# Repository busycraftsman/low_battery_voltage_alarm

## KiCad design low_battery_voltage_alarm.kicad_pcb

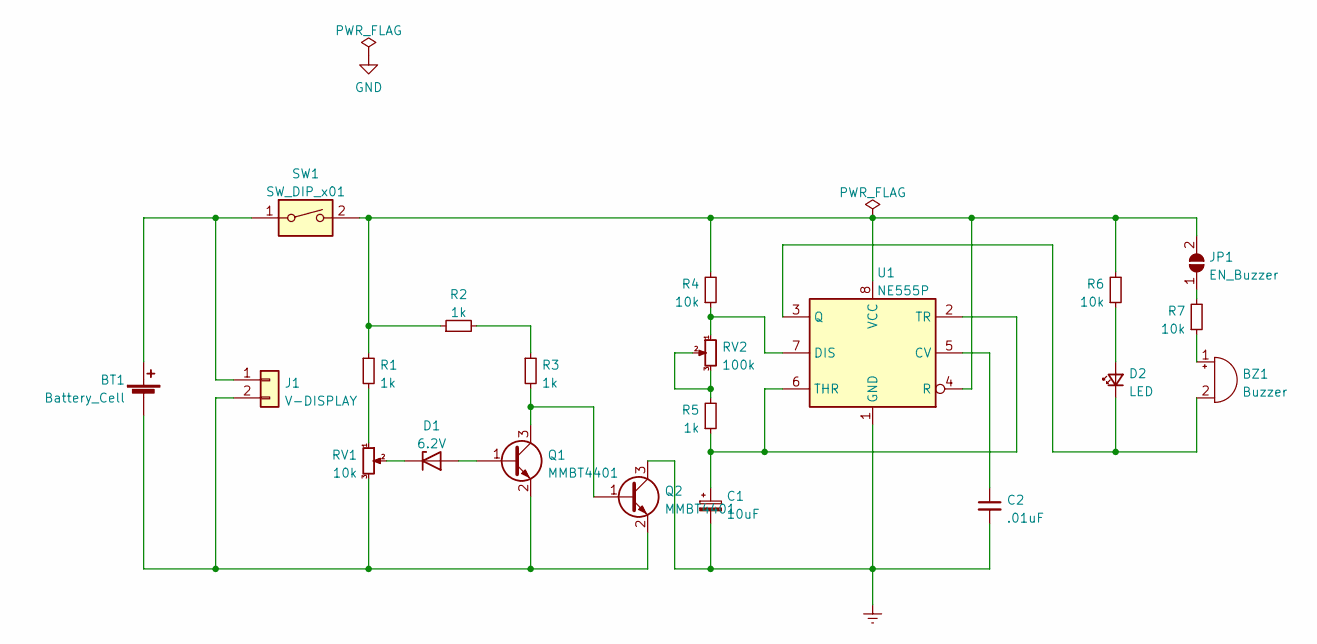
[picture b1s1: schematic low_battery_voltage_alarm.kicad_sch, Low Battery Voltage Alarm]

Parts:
BT1: Battery_Cell; JST_XH_S2B-XH-A-1_1x02_P2.50mm_Horizontal
BZ1: Buzzer; Buzzer_12x9.5RM7.6
C1: 10uF; CP_Radial_D5.0mm_P2.50mm
C2: .01uF; C_0805_2012Metric_Pad1.18x1.45mm_HandSolder
D1: 6.2V; D_DO-35_SOD27_P7.62mm_Horizontal
D2: LED; LED_D1.8mm_W3.3mm_H2.4mm
J1: V-DISPLAY; JST_XH_S2B-XH-A-1_1x02_P2.50mm_Horizontal
JP1: EN_Buzzer; SolderJumper-2_P1.3mm_Open_RoundedPad1.0x1.5mm
Q1, Q2: MMBT4401; SOT-23
R1, R2, R3, R5: 1k; R_0805_2012Metric_Pad1.20x1.40mm_HandSolder
R4, R6, R7: 10k; R_0805_2012Metric_Pad1.20x1.40mm_HandSolder
RV1: 10k; Potentiometer_Runtron_RM-065_Vertical
RV2: 100k; Potentiometer_Runtron_RM-065_Vertical
SW1: SW_DIP_x01; SolderWire-0.1sqmm_1x02_P3.6mm_D0.4mm_OD1mm
U1: NE555P; DIP-8_W7.62mm

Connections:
GNDREF: C1.2, C2.2, Q2.3 (C), U1.1 (GND)
unnamed: BT1.1 (+), J1.1, SW1.1
unnamed: BT1.2 (-), J1.2, Q1.2 (E), Q2.2 (E), RV1.3
unnamed: BZ1.1 (-), R7.1
unnamed: BZ1.2 (+), D2.1 (K), U1.3 (Q)
unnamed: C1.1, R5.1, U1.2 (TR), U1.6 (THR)
unnamed: C2.1, U1.5 (CV)
unnamed: D1.1 (K), RV1.2
unnamed: D1.2 (A), Q1.1 (B)
unnamed: D2.2 (A), R6.1
unnamed: Q1.3 (C), Q2.1 (B), R3.2
unnamed: JP1.2 (B), R1.1, R2.1, R4.2, R6.2, SW1.2, U1.4 (R), U1.8 (VCC)
unnamed: R1.2, RV1.1
unnamed: R2.2, R3.1
unnamed: R4.1, RV2.1, U1.7 (DIS)
unnamed: R5.2, RV2.2, RV2.3
unnamed: JP1.1 (A), R7.2

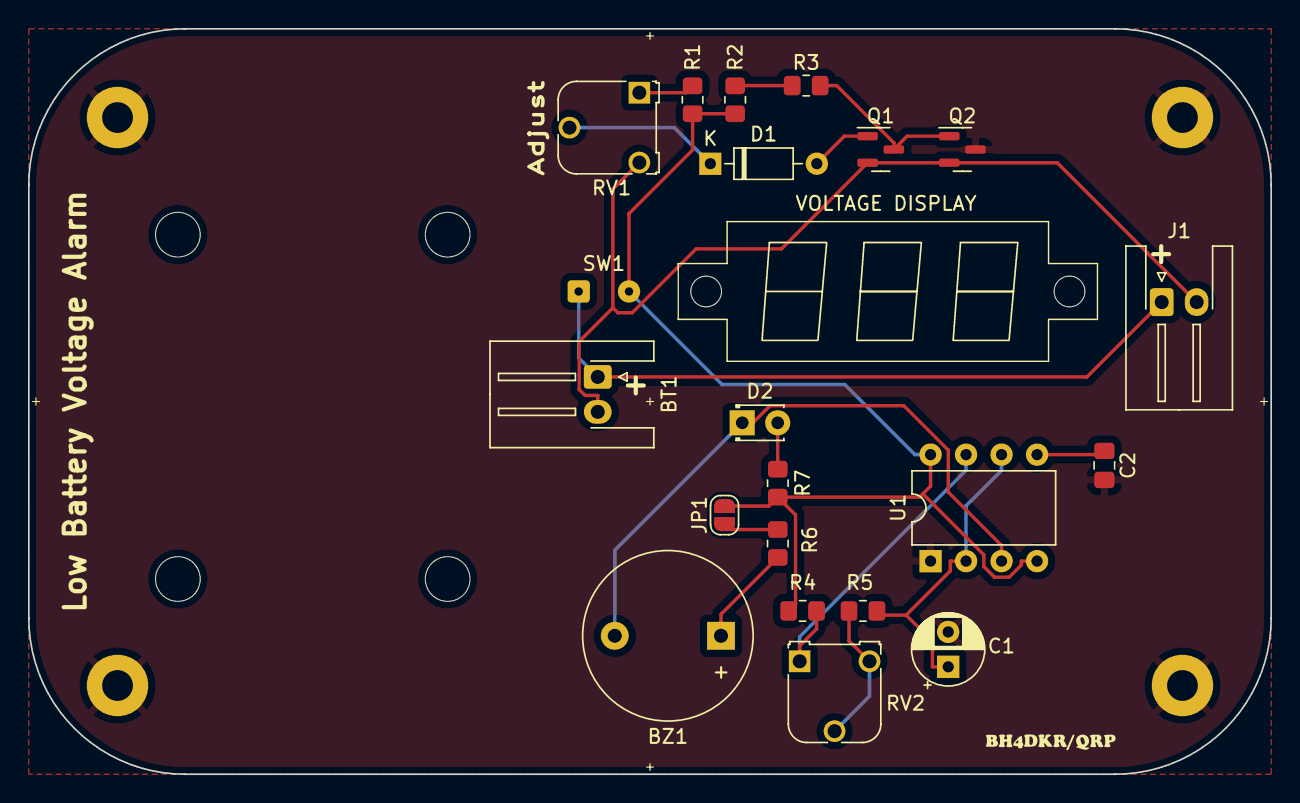
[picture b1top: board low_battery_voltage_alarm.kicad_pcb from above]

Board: 2 copper layers, 88.9 x 53.3 mm, 23 parts (0 on the bottom side), 17 nets.

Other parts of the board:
REF_BOX: ALTOIDS_round_89mmx54mmx19mm_hole_2.0mm; ALTOIDS_round_rectangle_89mmx54mmx19mm
VOLTAGE DISPLAY: 0.28_DC_VOLTAGE_2_WIRE_METER

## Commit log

2022-11-10 Version 1
2022-11-17 1. add comment dimension; 2. add front/back position file (for box drill);
2022-11-22 change 2N4401 => MMBT4401
2022-11-23 regenerate gerb files;
2022-12-03 change footprint error and add jumper to buzzer(mini power)
